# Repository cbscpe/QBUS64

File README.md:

# Bus CARD for the QBUS64 of the PDP-11/Hack

A small bus card with 5 slots for the PDP-11/Hack. 

## QBUS64

The QBUS64 is derived from the Q-BUS of PDP-11. The QBUS64 uses the same
protocol and timing as the real Q-BUS. Main differences are

- The bus uses Eurocard sized PCBs
- QBUS64 uses DIN41612 connectors
- QBUS64 provides only 5V

## Power

The QBUS64 can either be powered via an USB-C power plug or via the
terminal block. 

## VBAT

The QBUS64 has a VBAT signal that allows to provide battery backup power
to the cards. The QBUS64 card has a vertical coin battery holder for
CR2032 cells. This cell allows for more battery baackup power than the
battery backup from the CR1220 used for the RTC on the PDP-11 CPU V2-3.

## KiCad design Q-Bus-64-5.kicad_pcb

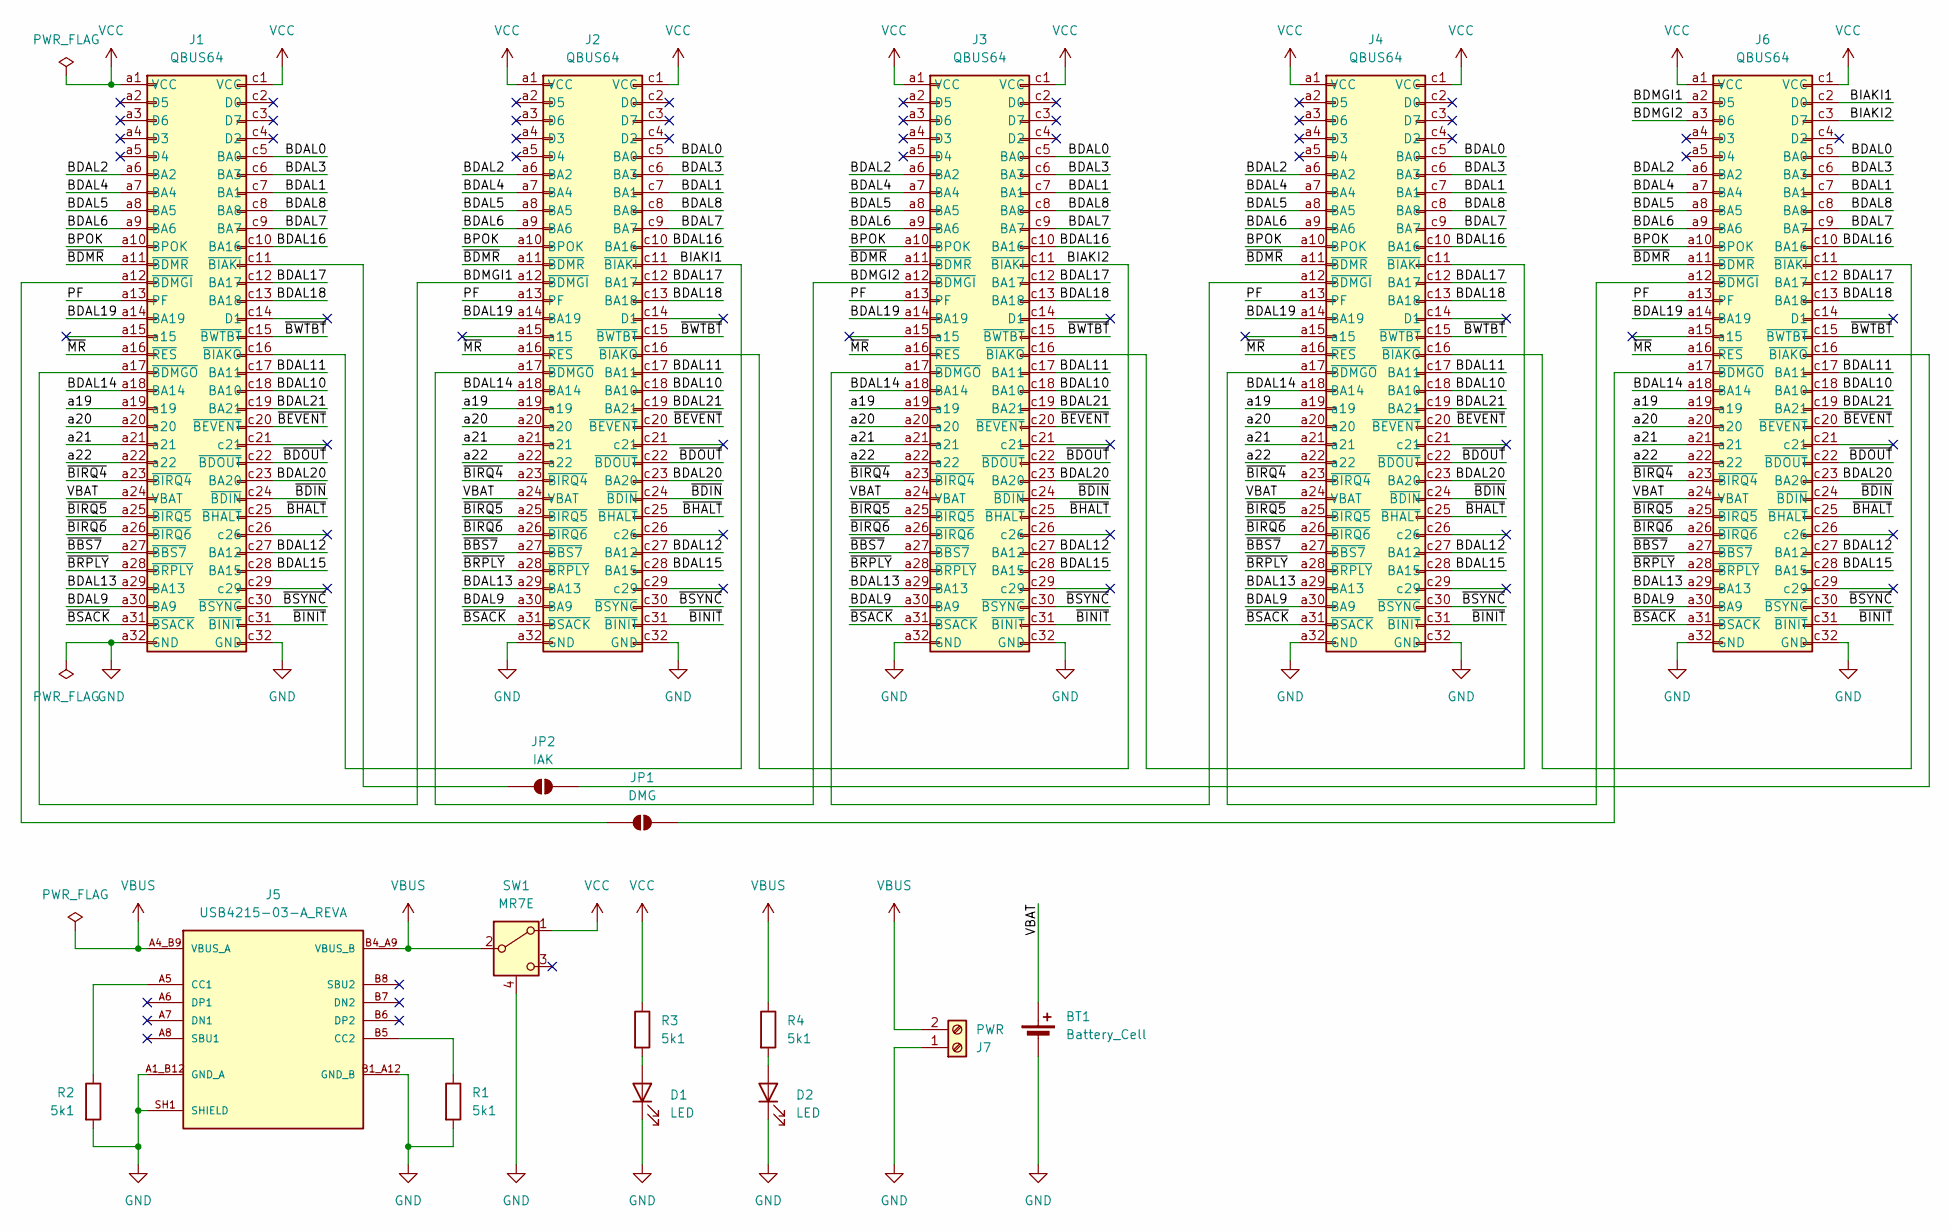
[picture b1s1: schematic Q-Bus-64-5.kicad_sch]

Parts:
BT1: Battery_Cell; VBH2023-1
D1, D2: LED; LED_1206_3216Metric_Pad1.42x1.75mm_HandSolder
J1, J2, J3, J4, J6: QBUS64; DIN41612_C_2x32_Female_Vertical_THT
J5: USB4215-03-A_REVA; GCT_USB4215-03-A-REVB
J7: PWR; TerminalBlock_MaiXu_MX126-5.0-02P_1x02_P5.00mm
JP1: DMG; SolderJumper-2_P1.3mm_Open_RoundedPad1.0x1.5mm
JP2: IAK; SolderJumper-2_P1.3mm_Open_RoundedPad1.0x1.5mm
R1, R2, R3, R4: 5k1; R_0603_1608Metric_Pad0.98x0.95mm_HandSolder
SW1: MR7E

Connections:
/BDAL0: J1.c5 (BA0), J2.c5 (BA0), J3.c5 (BA0), J4.c5 (BA0), J6.c5 (BA0)
/BDAL1: J1.c7 (BA1), J2.c7 (BA1), J3.c7 (BA1), J4.c7 (BA1), J6.c7 (BA1)
/BDAL2: J1.a6 (BA2), J2.a6 (BA2), J3.a6 (BA2), J4.a6 (BA2), J6.a6 (BA2)
/BDAL3: J1.c6 (BA3), J2.c6 (BA3), J3.c6 (BA3), J4.c6 (BA3), J6.c6 (BA3)
/BDAL4: J1.a7 (BA4), J2.a7 (BA4), J3.a7 (BA4), J4.a7 (BA4), J6.a7 (BA4)
/BDAL5: J1.a8 (BA5), J2.a8 (BA5), J3.a8 (BA5), J4.a8 (BA5), J6.a8 (BA5)
/BDAL6: J1.a9 (BA6), J2.a9 (BA6), J3.a9 (BA6), J4.a9 (BA6), J6.a9 (BA6)
/BDAL7: J1.c9 (BA7), J2.c9 (BA7), J3.c9 (BA7), J4.c9 (BA7), J6.c9 (BA7)
/BDAL8: J1.c8 (BA8), J2.c8 (BA8), J3.c8 (BA8), J4.c8 (BA8), J6.c8 (BA8)
/BDAL9: J1.a30 (BA9), J2.a30 (BA9), J3.a30 (BA9), J4.a30 (BA9), J6.a30 (BA9)
/BDAL10: J1.c18 (BA10), J2.c18 (BA10), J3.c18 (BA10), J4.c18 (BA10), J6.c18 (BA10)
/BDAL11: J1.c17 (BA11), J2.c17 (BA11), J3.c17 (BA11), J4.c17 (BA11), J6.c17 (BA11)
/BDAL12: J1.c27 (BA12), J2.c27 (BA12), J3.c27 (BA12), J4.c27 (BA12), J6.c27 (BA12)
/BDAL13: J1.a29 (BA13), J2.a29 (BA13), J3.a29 (BA13), J4.a29 (BA13), J6.a29 (BA13)
/BDAL14: J1.a18 (BA14), J2.a18 (BA14), J3.a18 (BA14), J4.a18 (BA14), J6.a18 (BA14)
/BDAL15: J1.c28 (BA15), J2.c28 (BA15), J3.c28 (BA15), J4.c28 (BA15), J6.c28 (BA15)
/BDAL16: J1.c10 (BA16), J2.c10 (BA16), J3.c10 (BA16), J4.c10 (BA16), J6.c10 (BA16)
/BDAL17: J1.c12 (BA17), J2.c12 (BA17), J3.c12 (BA17), J4.c12 (BA17), J6.c12 (BA17)
/BDAL18: J1.c13 (BA18), J2.c13 (BA18), J3.c13 (BA18), J4.c13 (BA18), J6.c13 (BA18)
/BDAL19: J1.a14 (BA19), J2.a14 (BA19), J3.a14 (BA19), J4.a14 (BA19), J6.a14 (BA19)
/BDAL20: J1.c23 (BA20), J2.c23 (BA20), J3.c23 (BA20), J4.c23 (BA20), J6.c23 (BA20)
/BDAL21: J1.c19 (BA21), J2.c19 (BA21), J3.c19 (BA21), J4.c19 (BA21), J6.c19 (BA21)
/BDMGI1: J1.a17 (~BDMGO), J2.a12 (~BDMGI), J6.a2 (D5)
/BDMGI2: J2.a17 (~BDMGO), J3.a12 (~BDMGI), J6.a3 (D6)
/BIAKI1: J1.c16 (~BIAKO), J2.c11 (~BIAKI), J6.c2 (D0)
/BIAKI2: J2.c16 (~BIAKO), J3.c11 (~BIAKI), J6.c3 (D7)
/BPOK: J1.a10 (BPOK), J2.a10 (BPOK), J3.a10 (BPOK), J4.a10 (BPOK), J6.a10 (BPOK)
/PF: J1.a13 (PF), J2.a13 (PF), J3.a13 (PF), J4.a13 (PF), J6.a13 (PF)
/VBAT: BT1.1 (+), J1.a24 (VBAT), J2.a24 (VBAT), J3.a24 (VBAT), J4.a24 (VBAT), J6.a24 (VBAT)
/a19: J1.a19, J2.a19, J3.a19, J4.a19, J6.a19
/a20: J1.a20, J2.a20, J3.a20, J4.a20, J6.a20
/a21: J1.a21, J2.a21, J3.a21, J4.a21, J6.a21
/a22: J1.a22, J2.a22, J3.a22, J4.a22, J6.a22
/~BBS7: J1.a27 (~BBS7), J2.a27 (~BBS7), J3.a27 (~BBS7), J4.a27 (~BBS7), J6.a27 (~BBS7)
/~BDIN: J1.c24 (~BDIN), J2.c24 (~BDIN), J3.c24 (~BDIN), J4.c24 (~BDIN), J6.c24 (~BDIN)
/~BDMR: J1.a11 (~BDMR), J2.a11 (~BDMR), J3.a11 (~BDMR), J4.a11 (~BDMR), J6.a11 (~BDMR)
/~BDOUT: J1.c22 (~BDOUT), J2.c22 (~BDOUT), J3.c22 (~BDOUT), J4.c22 (~BDOUT), J6.c22 (~BDOUT)
/~BEVENT: J1.c20 (~BEVENT), J2.c20 (~BEVENT), J3.c20 (~BEVENT), J4.c20 (~BEVENT), J6.c20 (~BEVENT)
/~BHALT: J1.c25 (~BHALT), J2.c25 (~BHALT), J3.c25 (~BHALT), J4.c25 (~BHALT), J6.c25 (~BHALT)
/~BINIT: J1.c31 (~BINIT), J2.c31 (~BINIT), J3.c31 (~BINIT), J4.c31 (~BINIT), J6.c31 (~BINIT)
/~BIRQ4: J1.a23 (~BIRQ4), J2.a23 (~BIRQ4), J3.a23 (~BIRQ4), J4.a23 (~BIRQ4), J6.a23 (~BIRQ4)
/~BIRQ5: J1.a25 (~BIRQ5), J2.a25 (~BIRQ5), J3.a25 (~BIRQ5), J4.a25 (~BIRQ5), J6.a25 (~BIRQ5)
/~BIRQ6: J1.a26 (~BIRQ6), J2.a26 (~BIRQ6), J3.a26 (~BIRQ6), J4.a26 (~BIRQ6), J6.a26 (~BIRQ6)
/~BRPLY: J1.a28 (~BRPLY), J2.a28 (~BRPLY), J3.a28 (~BRPLY), J4.a28 (~BRPLY), J6.a28 (~BRPLY)
/~BSACK: J1.a31 (~BSACK), J2.a31 (~BSACK), J3.a31 (~BSACK), J4.a31 (~BSACK), J6.a31 (~BSACK)
/~BSYNC: J1.c30 (~BSYNC), J2.c30 (~BSYNC), J3.c30 (~BSYNC), J4.c30 (~BSYNC), J6.c30 (~BSYNC)
/~BWTBT: J1.c15 (~BWTBT), J2.c15 (~BWTBT), J3.c15 (~BWTBT), J4.c15 (~BWTBT), J6.c15 (~BWTBT)
/~MR: J1.a16 (~RES), J2.a16 (~RES), J3.a16 (~RES), J4.a16 (~RES), J6.a16 (~RES)
GND: BT1.2 (-), D1.1 (K), D2.1 (K), J1.a32 (GND), J1.c32 (GND), J2.a32 (GND), J2.c32 (GND), J3.a32 (GND), J3.c32 (GND), J4.a32 (GND), J4.c32 (GND), J5.A1_B12 (GND_A), J5.B1_A12 (GND_B), J5.SH1 (SHIELD), J5.SH2 (SHIELD), J5.SH3 (SHIELD), J5.SH4 (SHIELD), J6.a32 (GND), J6.c32 (GND), J7.1, R1.2, R2.2, SW1.4 (MP)
unnamed: D1.2 (A), R3.2
unnamed: D2.2 (A), R4.2
unnamed: J1.a12 (~BDMGI), JP1.2 (B)
unnamed: J1.c11 (~BIAKI), JP2.1 (A)
unnamed: J3.a17 (~BDMGO), J4.a12 (~BDMGI)
unnamed: J3.c16 (~BIAKO), J4.c11 (~BIAKI)
unnamed: J4.a17 (~BDMGO), J6.a12 (~BDMGI)
unnamed: J4.c16 (~BIAKO), J6.c11 (~BIAKI)
unnamed: J5.A5 (CC1), R2.1
unnamed: J5.B5 (CC2), R1.1
unnamed: J6.a17 (~BDMGO), JP1.1 (A)
unnamed: J6.c16 (~BIAKO), JP2.2 (B)
VBUS: J5.A4_B9 (VBUS_A), J5.B4_A9 (VBUS_B), J7.2, R4.1, SW1.2 (B)
VCC: J1.a1 (VCC), J1.c1 (VCC), J2.a1 (VCC), J2.c1 (VCC), J3.a1 (VCC), J3.c1 (VCC), J4.a1 (VCC), J4.c1 (VCC), J6.a1 (VCC), J6.c1 (VCC), R3.1, SW1.1 (A)

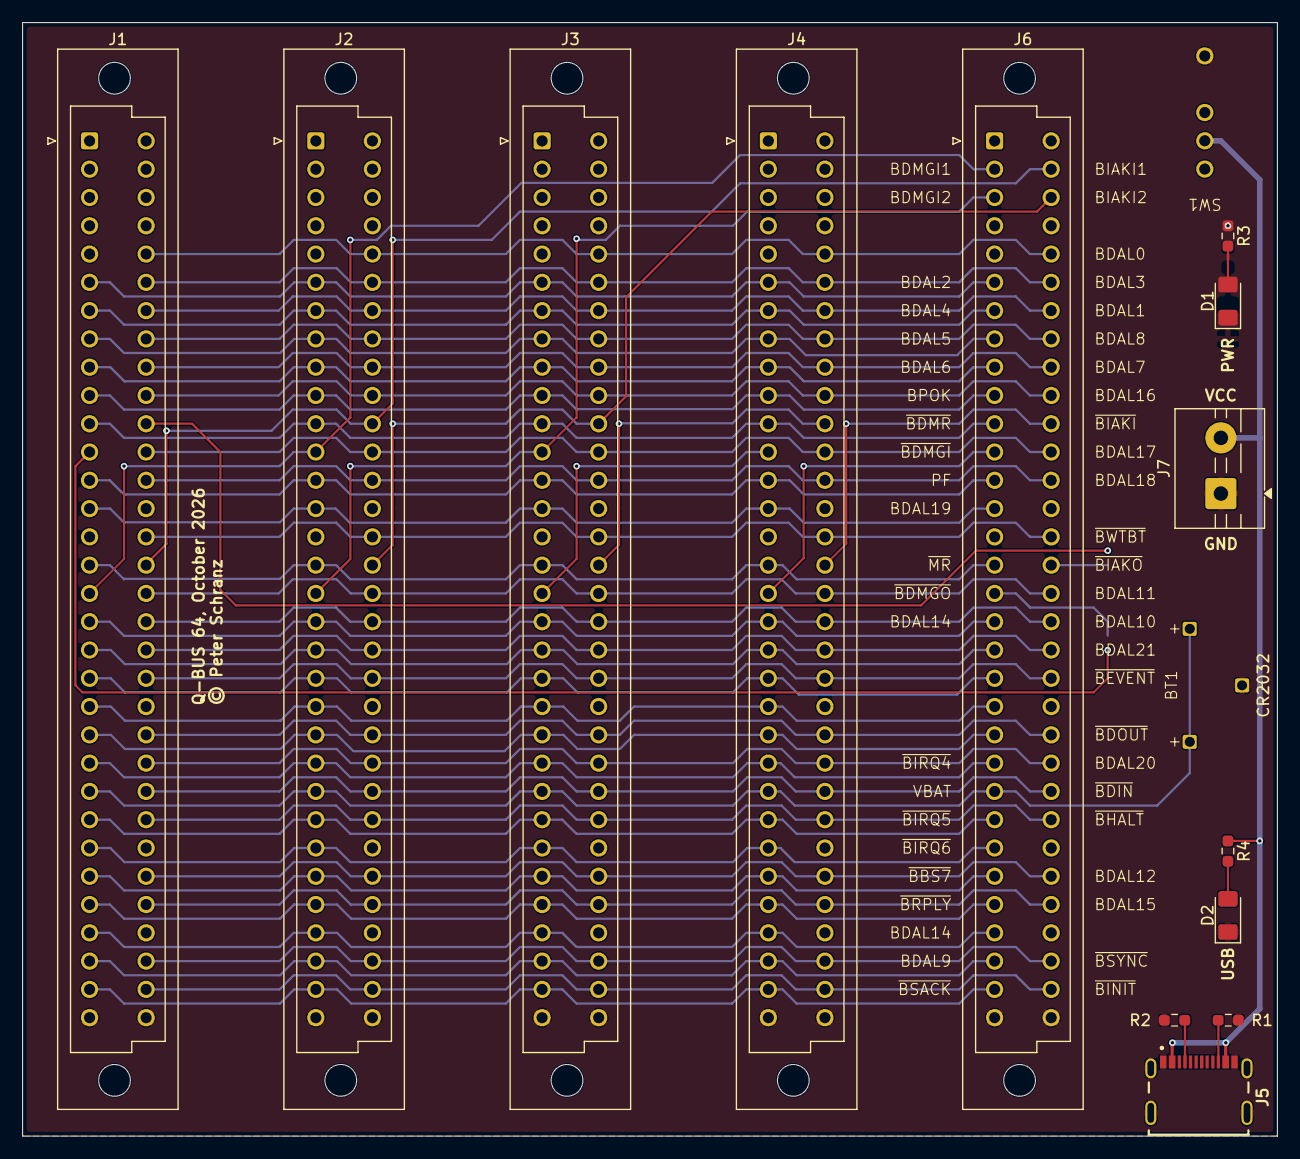
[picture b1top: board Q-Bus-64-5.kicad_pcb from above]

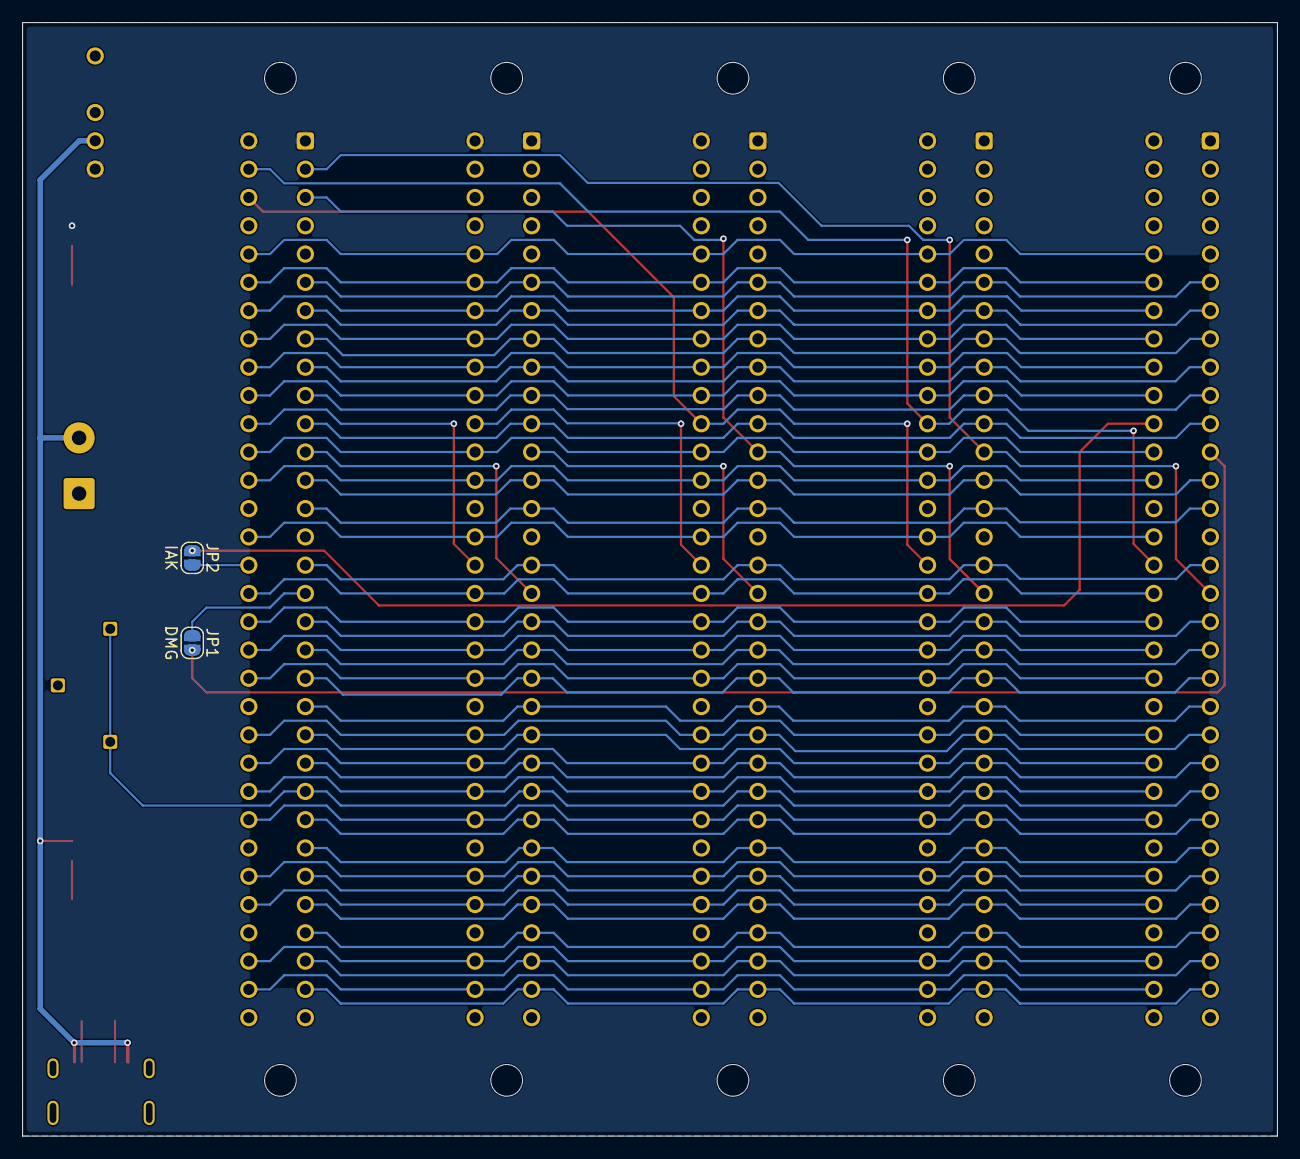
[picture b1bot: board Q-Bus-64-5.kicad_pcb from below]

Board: 2 copper layers, 112.7 x 100.0 mm, 17 parts (2 on the bottom side), 63 nets.

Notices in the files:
Q-Bus-64-5.kicad_pcb:
© Peter Schranz
